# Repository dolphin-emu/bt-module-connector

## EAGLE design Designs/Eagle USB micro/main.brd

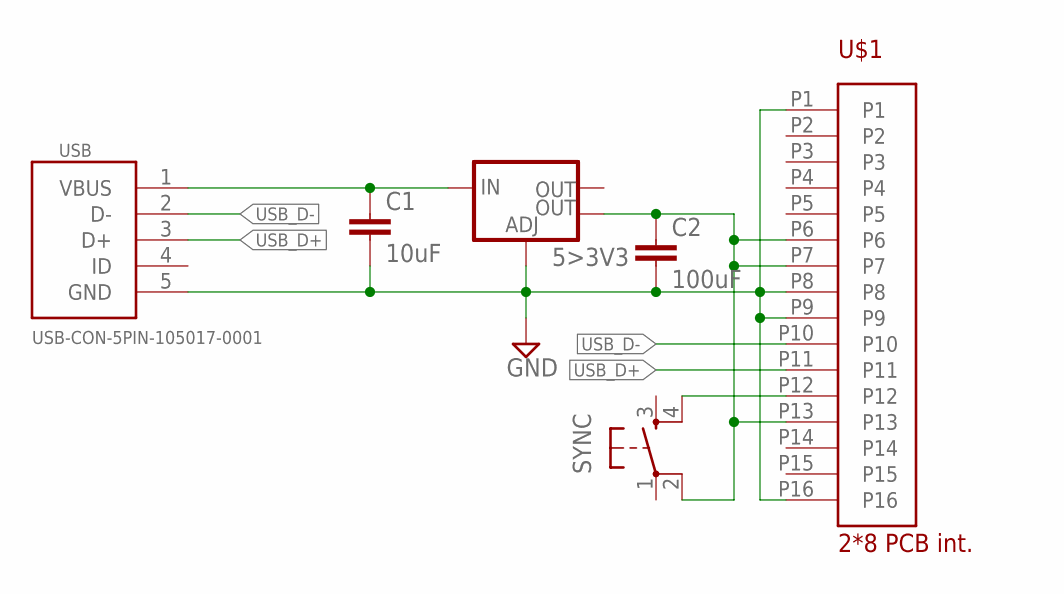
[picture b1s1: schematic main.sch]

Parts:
5>3V3: V_REG_LM1117SOT223; SOT223
C1: 10uF; C0805
C2: 100uF; C0805
SYNC: TAC_SWITCHPTH; TACTILE-PTH
U$1: MOLEX_0541020164MOLEX; MOLEX_0541020164
USB: USB-CON-5PIN-105017-0001; USB-MICRO-MOLEX-105017-0001

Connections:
3V3: 5>3V3.4 (OUT), C2.1, SYNC.2, U$1.P6, U$1.P7, U$1.P13
GND: 5>3V3.1 (ADJ), C1.2, C2.2, U$1.P1, U$1.P8, U$1.P9, U$1.P16, USB.5 (GND)
SYNC: SYNC.4, U$1.P12
USB_5V: 5>3V3.3 (IN), C1.1, USB.1 (VBUS)
USB_D+: U$1.P11, USB.3 (D+)
USB_D-: U$1.P10, USB.2 (D-)

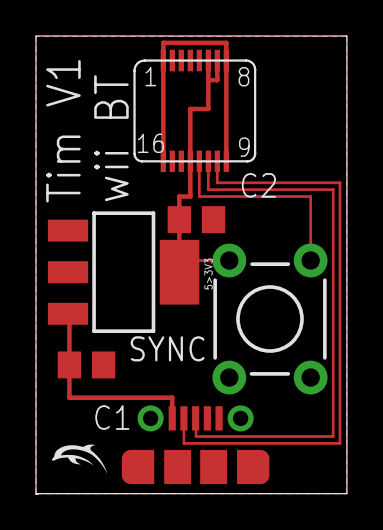
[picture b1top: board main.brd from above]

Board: 4 copper layers, 17.3 x 25.4 mm, 6 parts (0 on the bottom side), 6 nets.

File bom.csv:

Quantity	Value	Package	Order code	Supplier	Manufacturer	Manuf. Code	Availability	Price	Description
1	3.3V	SOT223	9778195	Farnell	TEXAS INSTRUMENTS	LM1117MP-3.3	7248	365	TEXAS INSTRUMENTS - LM1117MP-3.3 - V REG LDO +3.3V, 1117, SOT-223-3
1	10uF	C0805	2094042	Farnell	AVX	0805ZC106KAT2A	28421	111	AVX - 0805ZC106KAT2A - CAP, MLCC, X7R, 10UF, 10V, 0805
1	100uF	C0805	2494476	Farnell	Murata Electronics	GRM21BR60J107ME15L	16208	134	SMD Multilayer Ceramic Capacitor, 0805 [2012 Metric], 100 µF, 6.3 V, ± 20%, X5R, GRM Series
1	N/A	TACTILE-PTH	9471707	Farnell	MULTICOMP	MCDTS6-2N	68838	52	Tactile Switch, Non Illuminated, 12 V, 50 mA, 160 gf, Solder, MCDTS6 Series
1	MOLEX_0541020164MOLEX	MOLEX_0541020164	WM8876CT-ND 	Digi-Key	MOLEX	541020164	539	196	16 Position Connector Receptacle, Center Strip Contacts Surface Mount Gold 
1	USB-CON-5PIN-105017-0001	USB-MICRO-MOLEX-105017-0001	2293836	Farnell	MOLEX	105017-0001	8527	344	MOLEX - 105017-0001 - MICRO USB, 2.0 TYPE B, RECEPTACLE, SMT

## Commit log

2016-10-28 Added datasheet for slimstack connector
2016-11-09 Semi final design of the USB micro board by Ardent
2016-11-09 Designs: Add image exports.
2016-11-09 Fixed type, filled in the groundplane
2016-11-09 Designs: Update board image export.
2016-11-10 Added Bill-of-Materials draft for the Micro USB version.
2016-11-10 BOM: Fill in the empty value cells.
2016-11-15 Fixed dimensions plane missing line
2016-11-15 BOM: Use Farnell as the main supplier.
2016-11-15 BOM: Fix UTF-8 encoding.
2016-11-15 Added dolphin logo
2016-11-15 Designs: Update USB micro board image.
2016-12-26 Add draft design for PCI Express Mini Card.
2016-12-26 PCIe: Resize traces to better match the pads.

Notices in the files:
parts and their libraries:
SparkFun-PowerIC: Licensing: Creative Commons ShareAlike 4.0 International - https://creativecommons.org/licenses/by-sa/4.0
